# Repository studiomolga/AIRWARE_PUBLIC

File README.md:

# AIRWARE_PUBLIC<br><br>

COMPONENTS - in fritzing. <br>
Solar panel https://www.kiwi-electronics.com/nl/zonnepaneel-6v-9-0w-3366?search=Solar%206v%209w<br>

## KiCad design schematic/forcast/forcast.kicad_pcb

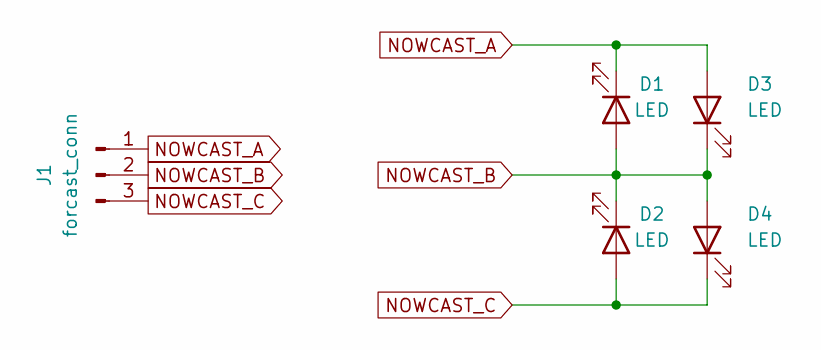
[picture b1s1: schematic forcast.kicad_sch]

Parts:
D1, D2, D3, D4: LED; LED_D5.0mm
J1: forcast_conn; JST_XH_B3B-XH-A_1x03_P2.50mm_Vertical

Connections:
NOWCAST_A: D1.1 (K), D3.2 (A), J1.1
NOWCAST_B: D1.2 (A), D2.1 (K), D3.1 (K), D4.2 (A), J1.2
NOWCAST_C: D2.2 (A), D4.1 (K), J1.3

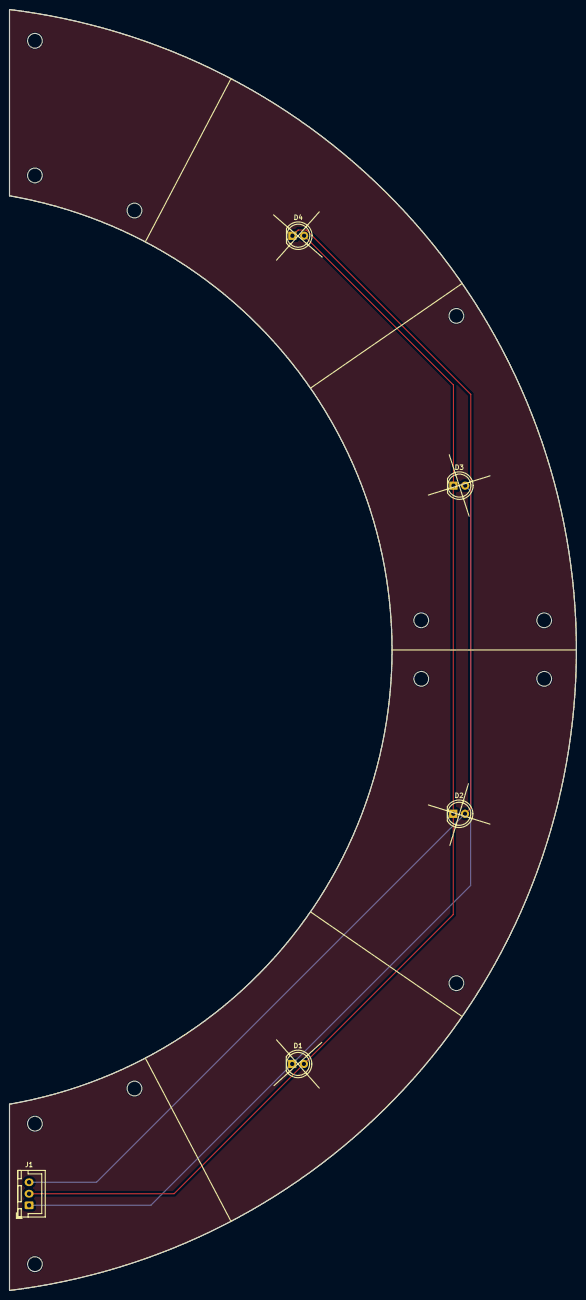
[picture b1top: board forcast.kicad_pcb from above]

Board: 2 copper layers, 123.0 x 277.9 mm, 5 parts (0 on the bottom side), 3 nets.

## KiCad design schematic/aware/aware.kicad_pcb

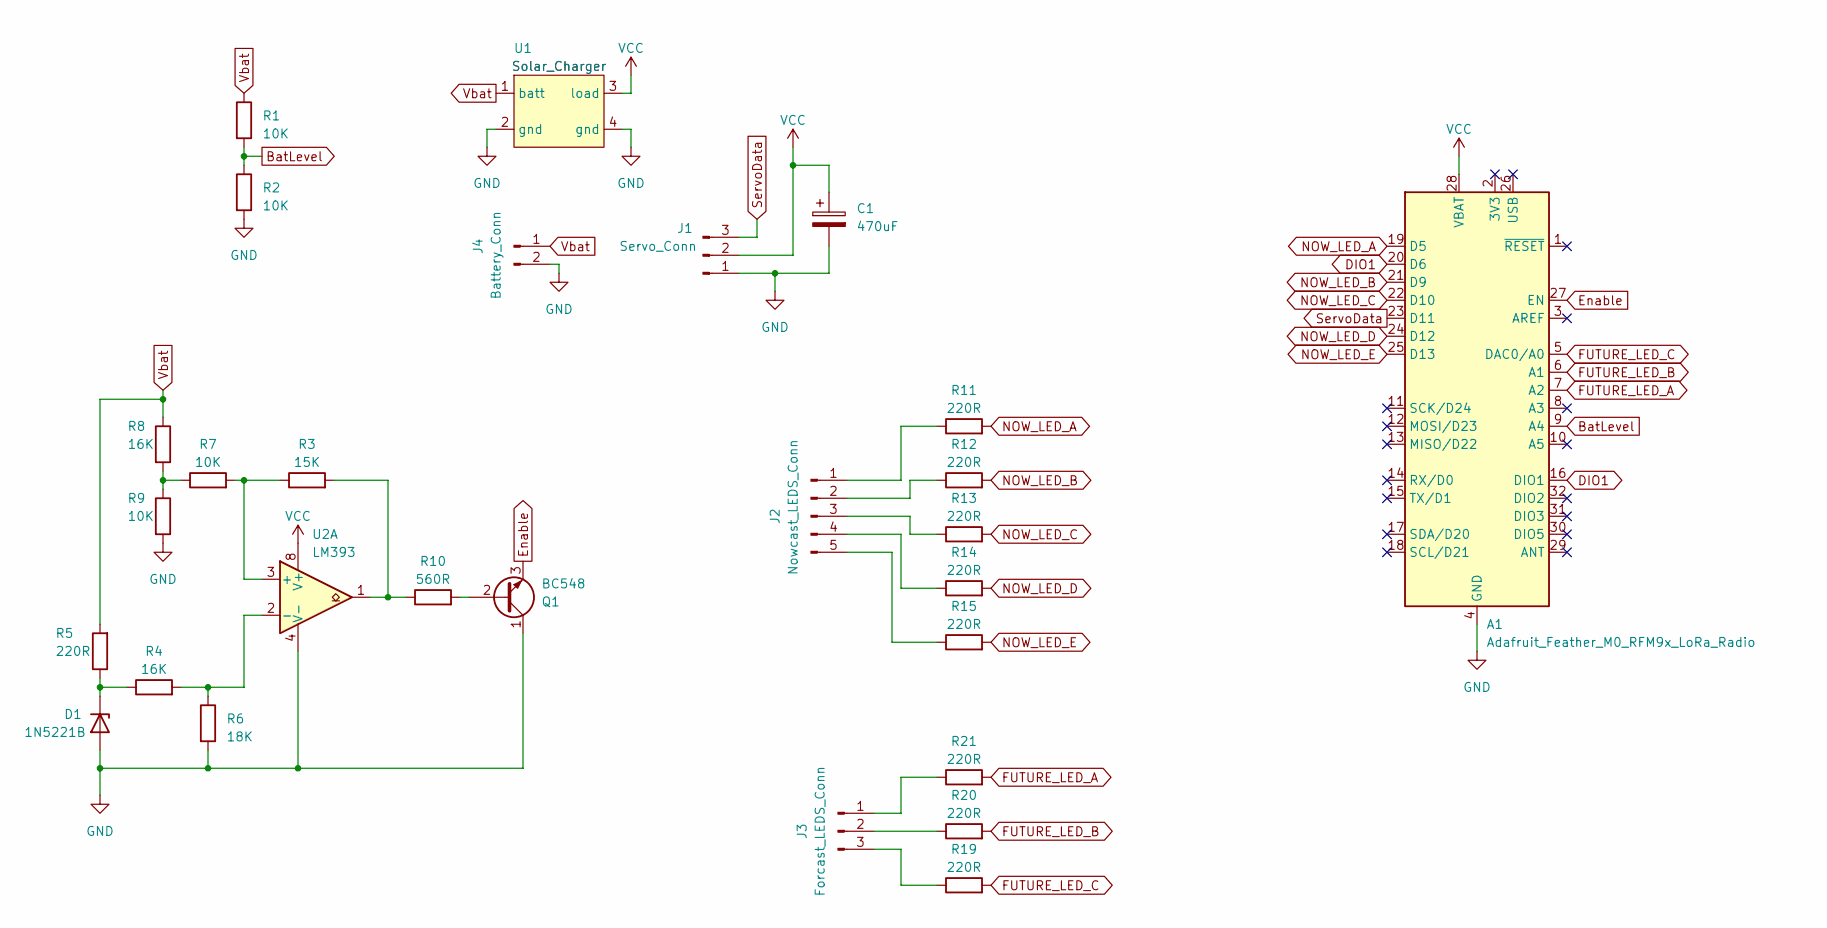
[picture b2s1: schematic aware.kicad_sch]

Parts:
A1: Adafruit_Feather_M0_RFM9x_LoRa_Radio; Adafruit_Feather_M0_RFM
C1: 470uF; CP_Radial_D10.0mm_P2.50mm
D1: 1N5221B; D_DO-35_SOD27_P7.62mm_Horizontal
J1: Servo_Conn; PinSocket_1x03_P2.54mm_Vertical
J2: Nowcast_LEDS_Conn; JST_XH_B5B-XH-A_1x05_P2.50mm_Vertical
J3: Forcast_LEDS_Conn; JST_XH_B3B-XH-A_1x03_P2.50mm_Vertical
J4: Battery_Conn; JST_XH_B2B-XH-A_1x02_P2.50mm_Vertical
Q1: BC548; TO-92_Inline_Wide
R1, R2, R7, R9: 10K; R_Axial_DIN0207_L6.3mm_D2.5mm_P7.62mm_Horizontal
R3: 15K; R_Axial_DIN0207_L6.3mm_D2.5mm_P7.62mm_Horizontal
R4, R8: 16K; R_Axial_DIN0207_L6.3mm_D2.5mm_P7.62mm_Horizontal
R5, R11, R12, R13, R14, R15, R19, R20, R21: 220R; R_Axial_DIN0207_L6.3mm_D2.5mm_P7.62mm_Horizontal
R6: 18K; R_Axial_DIN0207_L6.3mm_D2.5mm_P7.62mm_Horizontal
R10: 560R; R_Axial_DIN0207_L6.3mm_D2.5mm_P7.62mm_Horizontal
U1: Solar_Charger
U2: LM393; DIP-8_W7.62mm

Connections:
BatLevel: A1.9 (A4), R1.2, R2.1
DIO1: A1.16 (DIO1), A1.20 (D6)
Enable: A1.27 (EN), Q1.3 (E)
FUTURE_LED_A: A1.7 (A2), R21.2
FUTURE_LED_B: A1.6 (A1), R20.2
FUTURE_LED_C: A1.5 (DAC0/A0), R19.2
GND: A1.4 (GND), C1.2, D1.2 (A), J1.1, J4.2, Q1.1 (C), R2.2, R6.2, R9.2, U1.2 (gnd), U1.4 (gnd), U2.4 (V-)
NOW_LED_A: A1.19 (D5), R11.2
NOW_LED_B: A1.21 (D9), R12.2
NOW_LED_C: A1.22 (D10), R13.2
NOW_LED_D: A1.24 (D12), R14.2
NOW_LED_E: A1.25 (D13), R15.2
unnamed: D1.1 (K), R4.1, R5.1
unnamed: J2.1, R11.1
unnamed: J2.2, R12.1
unnamed: J2.3, R13.1
unnamed: J2.4, R14.1
unnamed: J2.5, R15.1
unnamed: J3.1, R21.1
unnamed: J3.2, R20.1
unnamed: J3.3, R19.1
unnamed: Q1.2 (B), R10.2
unnamed: R7.1, R8.2, R9.1
unnamed: R3.2, R10.1, U2.1
unnamed: R3.1, R7.2, U2.3 (+)
unnamed: R4.2, R6.1, U2.2 (-)
ServoData: A1.23 (D11), J1.3
VCC: A1.28 (VBAT), C1.1, J1.2, U1.3 (load), U2.8 (V+)
Vbat: J4.1, R1.1, R5.2, R8.1, U1.1 (batt)

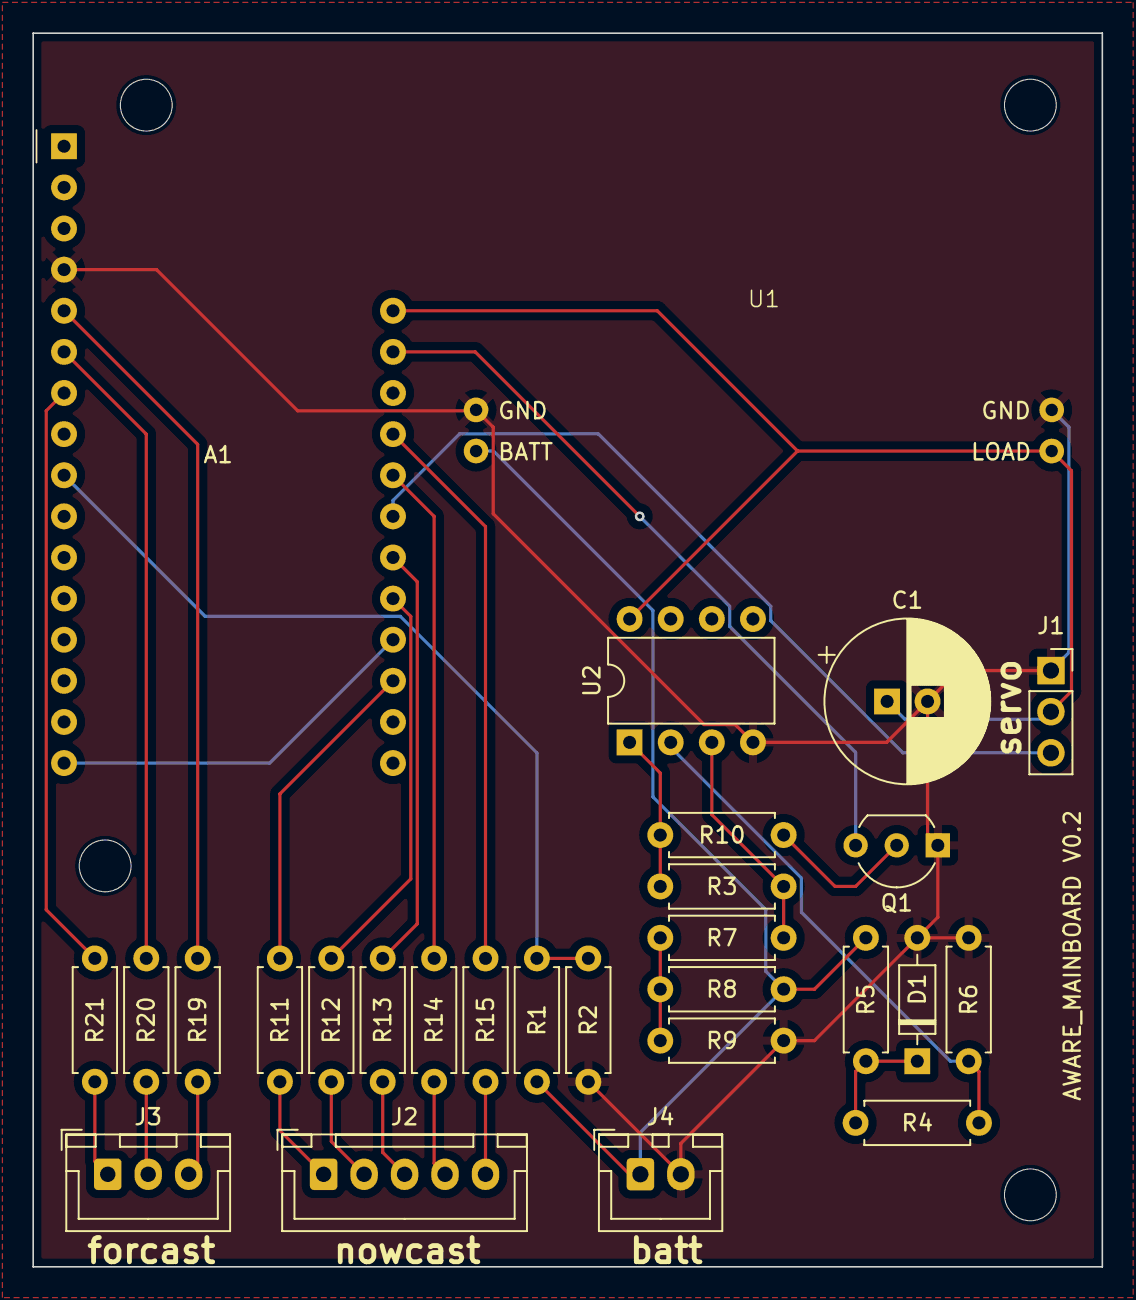
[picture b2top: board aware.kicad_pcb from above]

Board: 2 copper layers, 66.0 x 76.2 mm, 28 parts (0 on the bottom side), 29 nets.

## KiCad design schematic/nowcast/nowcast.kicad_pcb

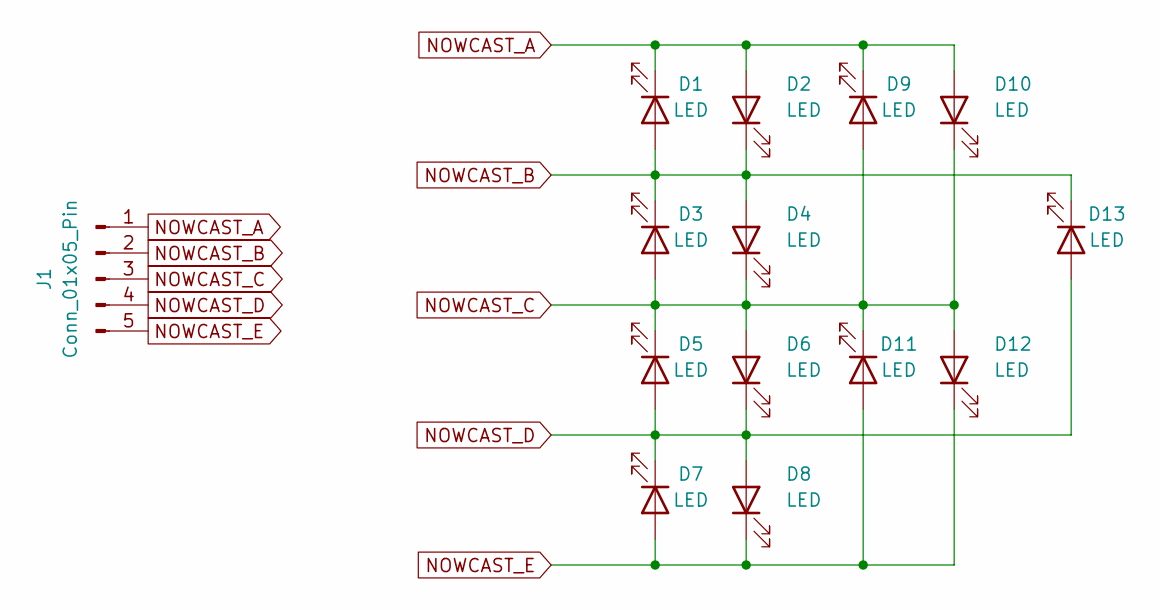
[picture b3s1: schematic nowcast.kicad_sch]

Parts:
D1, D2, D3, D4, D5, D6, D7, D8, D9, D10, D11, D12, D13: LED; LED_D5.0mm
J1: Conn_01x05_Pin; JST_XH_B5B-XH-A_1x05_P2.50mm_Vertical

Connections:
NOWCAST_A: D1.1 (K), D2.2 (A), D9.1 (K), D10.2 (A), J1.1
NOWCAST_B: D1.2 (A), D2.1 (K), D3.1 (K), D4.2 (A), D13.1 (K), J1.2
NOWCAST_C: D3.2 (A), D4.1 (K), D5.1 (K), D6.2 (A), D9.2 (A), D10.1 (K), D11.1 (K), D12.2 (A), J1.3
NOWCAST_D: D5.2 (A), D6.1 (K), D7.1 (K), D8.2 (A), D13.2 (A), J1.4
NOWCAST_E: D7.2 (A), D8.1 (K), D11.2 (A), D12.1 (K), J1.5

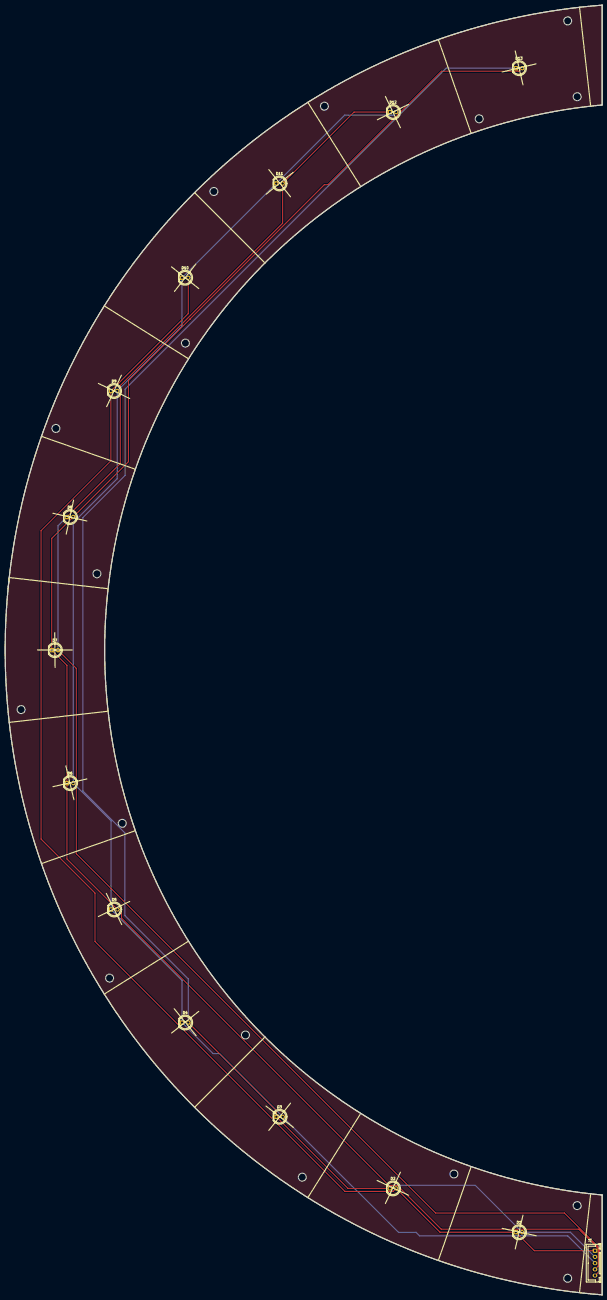
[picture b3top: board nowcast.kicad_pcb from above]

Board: 2 copper layers, 240.0 x 518.5 mm, 14 parts (0 on the bottom side), 5 nets.

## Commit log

2022-08-18 fixing small bugs
2022-08-18 fixed connection issues
2022-08-18 added generic pcb design
    has general output connector to which we can connect most things
2022-09-05 added new server script
2022-09-05 updated lora feather
2022-09-05 fixed scheduling
2022-09-05 changed scheduling
2022-09-05 repo clean up
2022-09-05 removed decoding uplink payload
2022-09-05 added timestamp to api call
2022-09-05 changed timestamp delta
2022-09-06 added connection refused exception to publish
2022-09-09 updated 1 byte downlink to feathers
2022-09-09 changed to 10 levels and 2 byte downlink
2022-09-09 fixed timing issue
2022-09-10 added error handling
2022-09-10 call set_devices in Application constructor
2022-09-10 changed order of species
2022-09-10 fixed led 3 and 4 not updating
2022-09-10 reverted species order back to original
2022-09-11 clean up
2022-09-11 handling mqtt error
2022-09-16 fixed handling negative nowcast values
2022-11-14 fixed key error crash
2022-11-27 added sleep cycles
    - led: uses RTC to control a sleep cycle, sleep at 23:00, wake up at
    06:00
    - lora: uses the watchdog timer to sleep in between messages
2023-01-10 small changes to icnrease power efficiency
2023-02-26 changes made on server pi
2023-02-26 changed server to nowcast and future cast
2023-02-26 change server to nowcast and futurecast
2023-03-13 added futurecast and using single feather
2023-03-18 changed ranges
2023-03-18 uncommitted fixes
2023-03-21 added o3 level 5 start
2023-04-14 cleaned up arduino folder
2023-04-14 added kicad project and cleaned up schematic folder
2023-04-14 added nowcast kicad project and schematic
2023-04-15 added forcast kicad project
2023-04-15 adjusted pinout of forcast connector on mainboard
2023-04-15 added edgecuts and silscreen to pcb file
2023-04-15 add silkscreen and edgecuts
2023-04-15 replaced design files for 13 led based
2023-04-15 adjusted pcb design
2023-04-19 added forcast request and processing
2023-04-19 repo cleanup
    - added .zip to gitignore
    - removed log file from repo
2023-04-19 added gerber files
2023-05-17 added minor fixes and updated gerbers
2023-07-23 reversed forcast led order to match pcb layout
